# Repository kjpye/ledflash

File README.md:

ledflash
========

bi-color led driver

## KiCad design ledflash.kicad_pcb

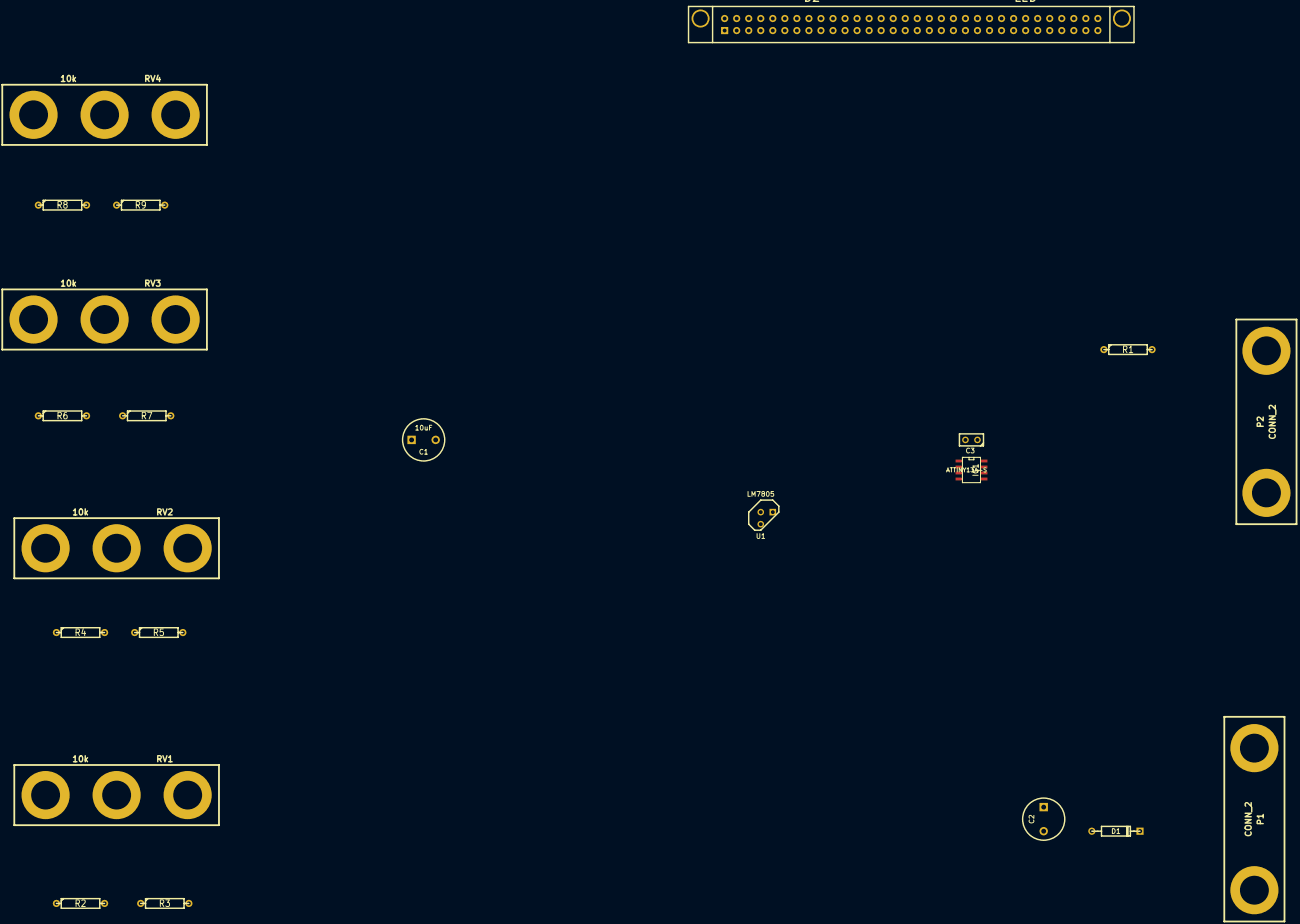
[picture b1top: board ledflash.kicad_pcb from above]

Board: 2 copper layers, 22 parts (0 on the bottom side), 10 nets, no tracks yet.

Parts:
C1, C2: 10uF; C2V8
C3: 0.1uF; C1
D1: BRIDGE; DO-41
D2: LED; c64abfd
IC1: ATTINY13A-S; SO8E
P1, P2: CONN_2; 2PIN_6mm
R1: 150; R4
R2, R3, R4, R5, R6, R7, R8, R9: 4k7; R4
RV1, RV2, RV3, RV4: 10k; 3PIN_6mm
U1: LM7805; TO92

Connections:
unnamed: IC1.3, R6.2, R7.1, RV3.2
unnamed: IC1.1, R8.2, R9.1, RV4.2
unnamed: P2.1, R1.2
unnamed: IC1.2, R4.2, R5.1, RV2.2
unnamed: IC1.7, R2.2, R3.1, RV1.2
unnamed: IC1.5, P2.2
unnamed: IC1.6, R1.1
unnamed: D1.2, P1.1
unnamed: C1.2, C2.2, C3.2, D1.1, IC1.4, R3.2, R5.2, R7.2, R9.2, RV1.3, RV2.3, RV3.3, RV4.3
unnamed: C2.1, C3.1, IC1.8, R2.1, R4.1, R8.1, RV1.1, RV2.1, RV3.1, RV4.1

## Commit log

2013-12-03 Initial github commit
2013-12-03 Component values
2013-12-03 power connector added
